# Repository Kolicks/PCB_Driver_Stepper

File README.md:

# 🌀 PCB_Driver_Stepper
**General Stepper Motor Driver Board**

## 🎬 Demo Video
[▶️ Watch Demo](Test_media/NEMA_Stepper.mp4)

<p align="center">
  <video src="https://github.com/user-attachments/assets/646c0d09-2157-4537-b24f-0206d356a9b6" width="600" controls></video>
  <br>
  <em>Demo NEMA Stepper</em>
</p>

---

## 📘 Overview
**PCB_Driver_Stepper** is a general-purpose stepper motor driver board designed in **KiCad 9**.  
This project was created to explore stepper motor control concepts, test design ideas from friends, and gain real experience with PCB design and STM32 microcontroller integration.  
It also represents my first complete project combining **hardware and STM32 firmware** using **STM32CubeIDE**.

<p align="center">
  
  <br>
  <em>3D render of the finished PCB_Driver_Stepper board</em>
</p>

---

## ⚙️ General Information
- First real **KiCad 9** project.
- Implemented to test and validate several design ideas.
- Tested multiple implementations, including **ULN2002** and different **power dissipation** techniques.
- Designed with **4 layers**, though a **2-layer** version could be achieved.
- Typical **FR4 PCB**, **1.6 mm thickness**, standard prepreg stackup.
- Serves as my first practical integration within **STM32CubeIDE**, using **STM32F030K6T6** as the MCU.

<p align="center">
  
  <br>
  <em>Schematic, Block diagram (KiCad 9)</em>
</p>

---

## 🔧 Characteristics
- **Fully functional**, fabricated and tested successfully.
- Tested with **STEPPERONLINE NEMA 17** (2A, 59 N·cm) — achieves over **300 RPM** without load.
- Capable of controlling **two stepper motors** simultaneously.
- Supports up to **2 A per motor**, limited by drivers and onboard potentiometers.
- **Operating voltage:** 12 VDC to 24 VDC (ideal at 24 V).
- Requires **external cooling** (top and bottom) for continuous operation (Alimunium or Copper Radiators used in real test).
- Integrated with **ULN2002A** as input mode (tested and working).
- Uses **pin connectors under driver GND pads** to allow hand-soldering.
- Optional **Schottky diodes** for additional protection and power isolation.

<p align="center">
  
  <br>
  <em>PCB layout design</em>
</p>

---

---

## 🔧 Panelization
- **Fully functional**, designed for **JLCPCB** fabrication process.  
- Created as an **exercise in PCB manufacturing and panelization design**.  
- Explored **V-cut (scoring) limitations**, fabrication tolerances, and how they affect mechanical integrity and assembly.  
- Observed potential **issues with scoring alignment and stress concentration** across panelized edges.  
- **Not required for this project**, as the board’s size and simplicity make panelization **unnecessary and potentially inefficient** for performance or cost.  

<p align="center">
  
  <br>
  <em>Panel layout design</em>
</p>

---

## ⚠️ Known Issues / Notes
- Thermal pads on the **Rsense GND pads** restrict efficient heat dissipation.
- Ideally should maintain a **4-layer design** to ensure proper driver thermal management (as recommended in datasheets).
- Too many bypass Capacitors on the MCU.
- **No status LEDs** (e.g., Power or Fault indicators) currently included — consider adding in future revisions.

---

## 🧩 Files and Structure

<p align="center">
  
</p>

PCB_Driver_Stepper/

├── schematic/ # KiCad schematic files

├── pcb_layout/ # KiCad PCB layout files

├── gerbers/ # Gerber fabrication files

├── images/ # Rendered visuals (3D, SCH, PCB)

├── LICENSE # Hardware license (CERN-OHL-P v2.0)

└── README.md # Project documentation

---

## 📜 License
This hardware design is released under the **CERN Open Hardware License v2 – Permissive (CERN-OHL-P-2.0)**.  
You are free to use, modify, and distribute this design, provided that:
- The license is included with redistributions.
- Proper credit is given to the original author.

More info: https://cern-ohl.web.cern.ch/

---

## 👤 Author
**Project:** PCB_Driver_Stepper  
**Author:** Kolicks  
**Toolchain:** KiCad 9  
**Version:** 9.0  

---

## 🧱 Future Improvements

- **Thermal Design Enhancements:**  
  - Improve **thermal via networks** around driver ICs.  (Done in Panelization)
  - Add **dedicated copper areas** and optional heatsink support for improved temperature control.  (Done in Panelization)

- **User Feedback & Indicators:**  
  - Integrate **status LEDs** for power, enable, and fault signals.  
  - Add a **motor activity indicator** (blinking per step pulse).  

- **Electrical Optimization:**   
  - Consider **thicker copper (2 oz)** for better power handling.  
  - Optimize **Rsense trace routing** to reduce noise coupling.  (Done in Panelization)

- **Mechanical Improvements:**  
  - Adjust mounting hole positions for compatibility with standard enclosures.  
  - Add **labeling and silkscreen clarity** for easier connection identification.  

---

⭐ *If you find this project useful or educational, please consider starring the repository and sharing feedback!*

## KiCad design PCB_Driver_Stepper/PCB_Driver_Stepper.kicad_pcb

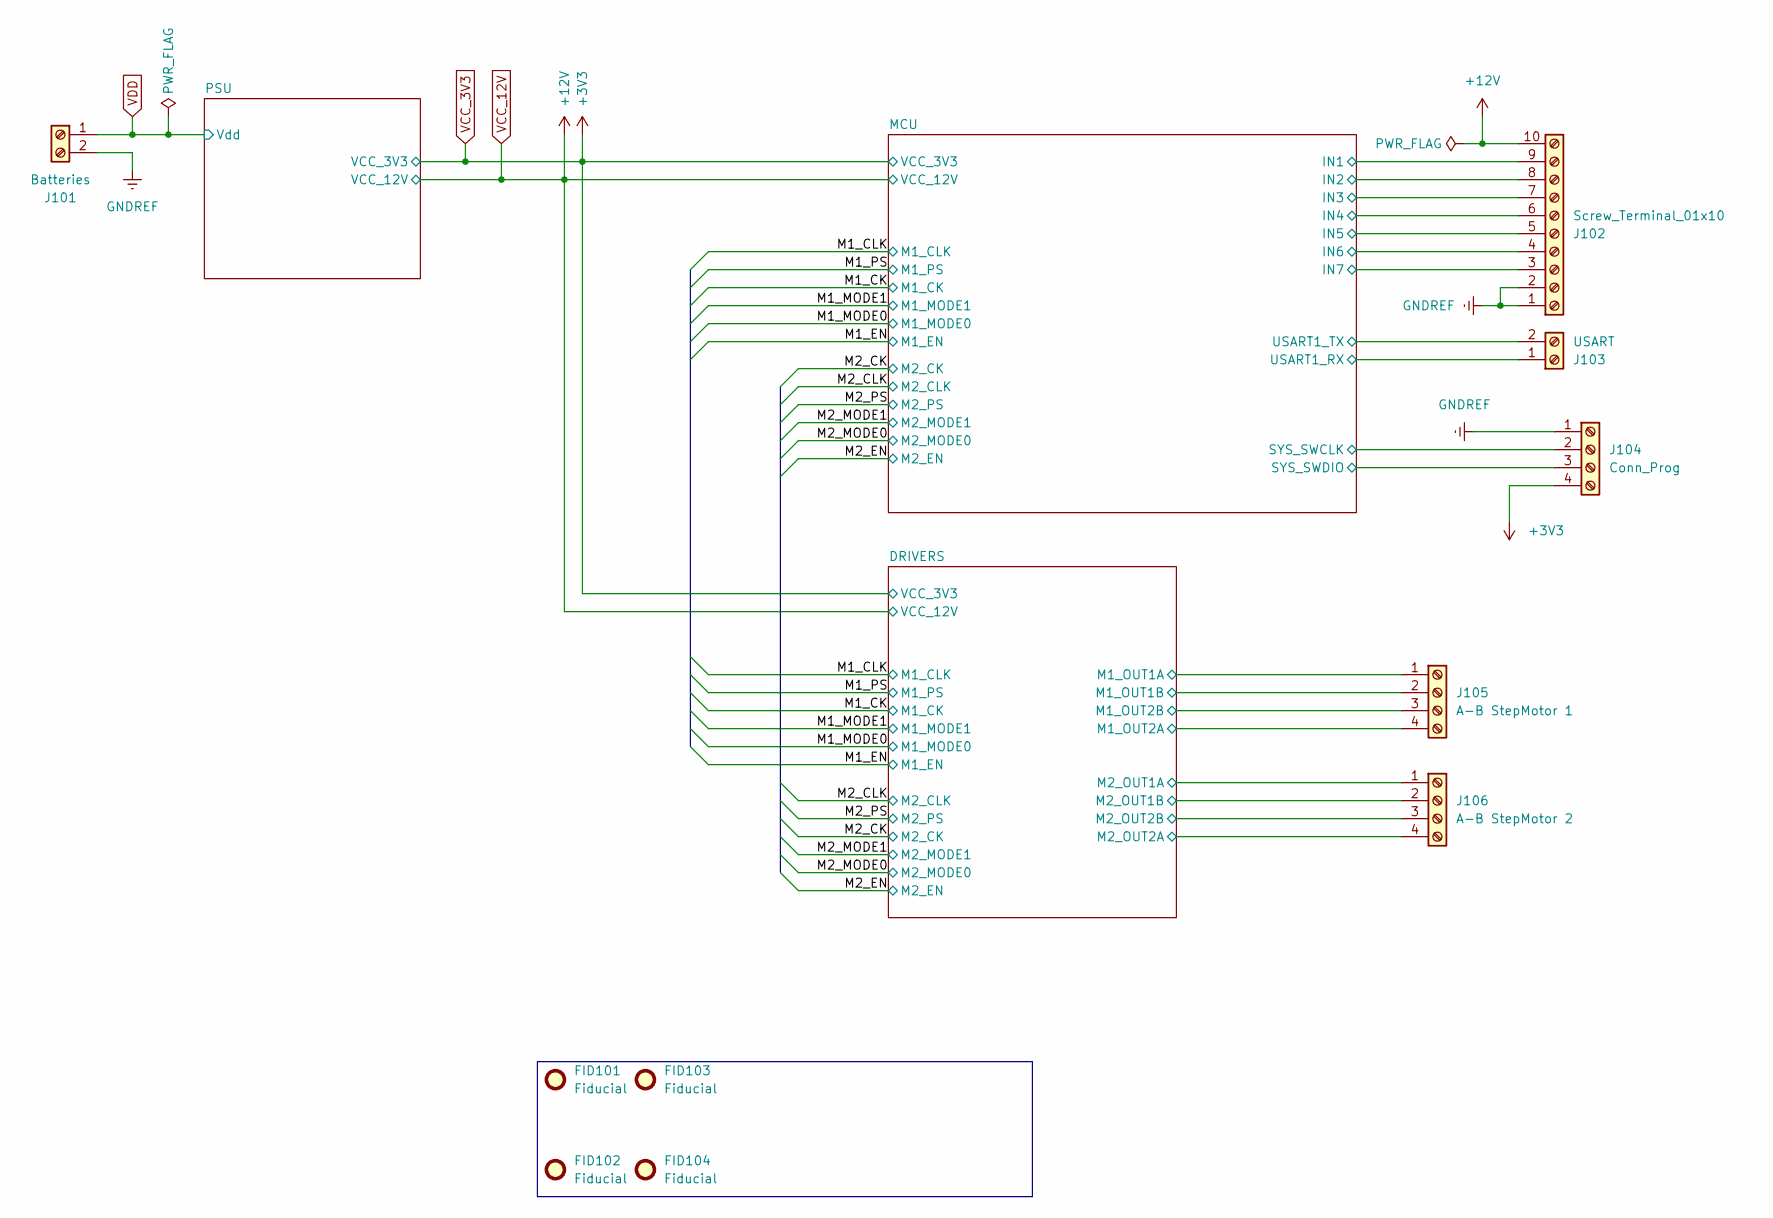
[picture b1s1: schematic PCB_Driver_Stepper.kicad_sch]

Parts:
FID101, FID102, FID103, FID104: Fiducial; Fiducial_1mm_Mask3mm
J101: Batteries; TerminalBlock_TE_282834-2_1x02_P2.54mm_Horizontal
J102: Screw_Terminal_01x10; TerminalBlock_TE_1-282834-0_1x10_P2.54mm_Horizontal
J103: USART; TerminalBlock_TE_282834-2_1x02_P2.54mm_Horizontal
J104: Conn_Prog; TerminalBlock_TE_282834-4_1x04_P2.54mm_Horizontal
J105: A-B StepMotor 1; TerminalBlock_TE_282834-4_1x04_P2.54mm_Horizontal
J106: A-B StepMotor 2; TerminalBlock_TE_282834-4_1x04_P2.54mm_Horizontal

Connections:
/DRIVERS/M1_OUT1A: J105.1; also elsewhere on the board
/DRIVERS/M1_OUT1B: J105.2; also elsewhere on the board
/DRIVERS/M1_OUT2A: J105.4; also elsewhere on the board
/DRIVERS/M1_OUT2B: J105.3; also elsewhere on the board
/DRIVERS/M2_OUT1A: J106.1; also elsewhere on the board
/DRIVERS/M2_OUT1B: J106.2; also elsewhere on the board
/DRIVERS/M2_OUT2A: J106.4; also elsewhere on the board
/DRIVERS/M2_OUT2B: J106.3; also elsewhere on the board
/MCU/IN1: J102.9; also elsewhere on the board
/MCU/IN2: J102.8; also elsewhere on the board
/MCU/IN3: J102.7; also elsewhere on the board
/MCU/IN4: J102.6; also elsewhere on the board
/MCU/IN5: J102.5; also elsewhere on the board
/MCU/IN6: J102.4; also elsewhere on the board
/MCU/IN7: J102.3; also elsewhere on the board
/MCU/SYS_SWCLK: J104.2; also elsewhere on the board
/MCU/SYS_SWDIO: J104.3; also elsewhere on the board
/MCU/USART1_RX: J103.1; also elsewhere on the board
/MCU/USART1_TX: J103.2; also elsewhere on the board
GNDREF: J101.2, J102.1, J102.2, J104.1; also elsewhere on the board
VCC_3V3: J104.4; also elsewhere on the board
VCC_12V: J102.10; also elsewhere on the board
VDD: J101.1; also elsewhere on the board

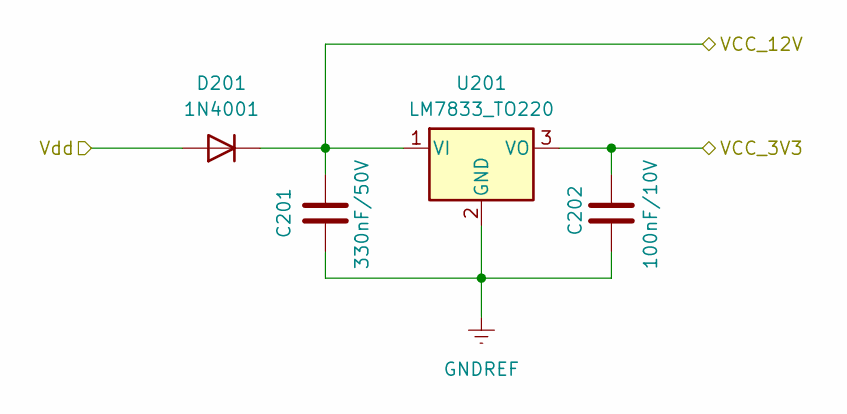
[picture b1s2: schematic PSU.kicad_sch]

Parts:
C201: 330nF/50V; C_0805_2012Metric
C202: 100nF/10V; C_0603_1608Metric
D201: 1N4001; D_SMA
U201: LM7833_TO220; TO-220-3_Vertical

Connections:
GNDREF: C201.2, C202.2, U201.2 (GND); also elsewhere on the board
VCC_3V3: C202.1, U201.3 (VO); also elsewhere on the board
VCC_12V: C201.1, D201.1 (K), U201.1 (VI); also elsewhere on the board
VDD: D201.2 (A); also elsewhere on the board

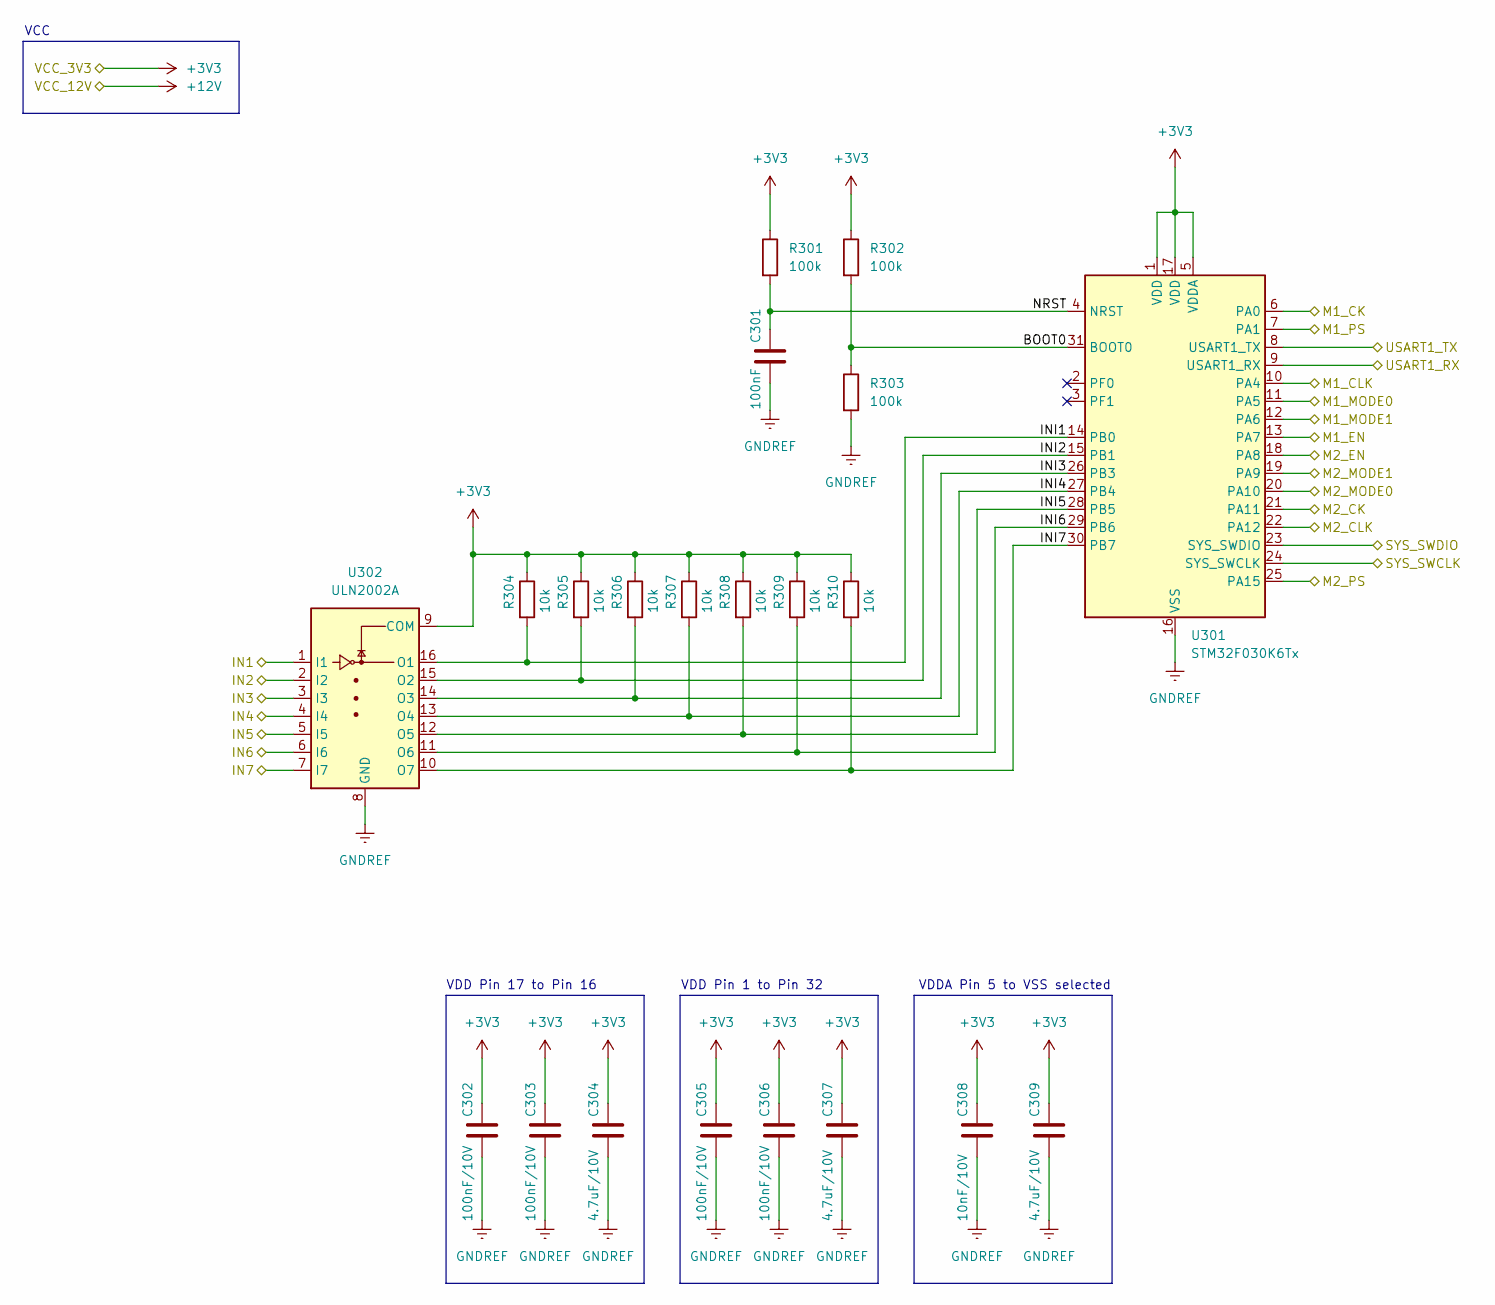
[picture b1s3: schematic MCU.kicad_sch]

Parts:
C301: 100nF; C_0603_1608Metric
C302, C303, C305, C306: 100nF/10V; C_0603_1608Metric
C304, C307, C309: 4.7uF/10V; C_0603_1608Metric
C308: 10nF/10V; C_0603_1608Metric
R301, R302, R303: 100k; R_0603_1608Metric
R304, R305, R306, R307, R308, R309, R310: 10k; R_0603_1608Metric
U301: STM32F030K6Tx; LQFP-32_7x7mm_P0.8mm
U302: ULN2002A; DIP-16_W7.62mm

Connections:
/M1_CK: U301.6 (PA0); also elsewhere on the board
/M1_CLK: U301.10 (PA4); also elsewhere on the board
/M1_EN: U301.13 (PA7); also elsewhere on the board
/M1_MODE0: U301.11 (PA5); also elsewhere on the board
/M1_MODE1: U301.12 (PA6); also elsewhere on the board
/M1_PS: U301.7 (PA1); also elsewhere on the board
/M2_CK: U301.21 (PA11); also elsewhere on the board
/M2_CLK: U301.22 (PA12); also elsewhere on the board
/M2_EN: U301.18 (PA8); also elsewhere on the board
/M2_MODE0: U301.20 (PA10); also elsewhere on the board
/M2_MODE1: U301.19 (PA9); also elsewhere on the board
/M2_PS: U301.25 (PA15); also elsewhere on the board
/MCU/BOOT0: R302.2, R303.1, U301.31 (BOOT0)
/MCU/IN1: U302.1 (I1); also elsewhere on the board
/MCU/IN2: U302.2 (I2); also elsewhere on the board
/MCU/IN3: U302.3 (I3); also elsewhere on the board
/MCU/IN4: U302.4 (I4); also elsewhere on the board
/MCU/IN5: U302.5 (I5); also elsewhere on the board
/MCU/IN6: U302.6 (I6); also elsewhere on the board
/MCU/IN7: U302.7 (I7); also elsewhere on the board
/MCU/INI1: R304.2, U301.14 (PB0), U302.16 (O1)
/MCU/INI2: R305.2, U301.15 (PB1), U302.15 (O2)
/MCU/INI3: R306.2, U301.26 (PB3), U302.14 (O3)
/MCU/INI4: R307.2, U301.27 (PB4), U302.13 (O4)
/MCU/INI5: R308.2, U301.28 (PB5), U302.12 (O5)
/MCU/INI6: R309.2, U301.29 (PB6), U302.11 (O6)
/MCU/INI7: R310.2, U301.30 (PB7), U302.10 (O7)
/MCU/NRST: C301.1, R301.2, U301.4 (NRST)
/MCU/SYS_SWCLK: U301.24 (SYS_SWCLK); also elsewhere on the board
/MCU/SYS_SWDIO: U301.23 (SYS_SWDIO); also elsewhere on the board
/MCU/USART1_RX: U301.9 (USART1_RX); also elsewhere on the board
/MCU/USART1_TX: U301.8 (USART1_TX); also elsewhere on the board
GNDREF: C301.2, C302.2, C303.2, C304.2, C305.2, C306.2, C307.2, C308.2, C309.2, R303.2, U301.16 (VSS), U301.32 (VSS), U302.8 (GND); also elsewhere on the board
VCC_3V3: C302.1, C303.1, C304.1, C305.1, C306.1, C307.1, C308.1, C309.1, R301.1, R302.1, R304.1, R305.1, R306.1, R307.1, R308.1, R309.1, R310.1, U301.1 (VDD), U301.5 (VDDA), U301.17 (VDD), U302.9 (COM); also elsewhere on the board

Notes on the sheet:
VDDA Pin 5 to VSS selected
VDD Pin 1 to Pin 32
VDD Pin 17 to Pin 16
VCC

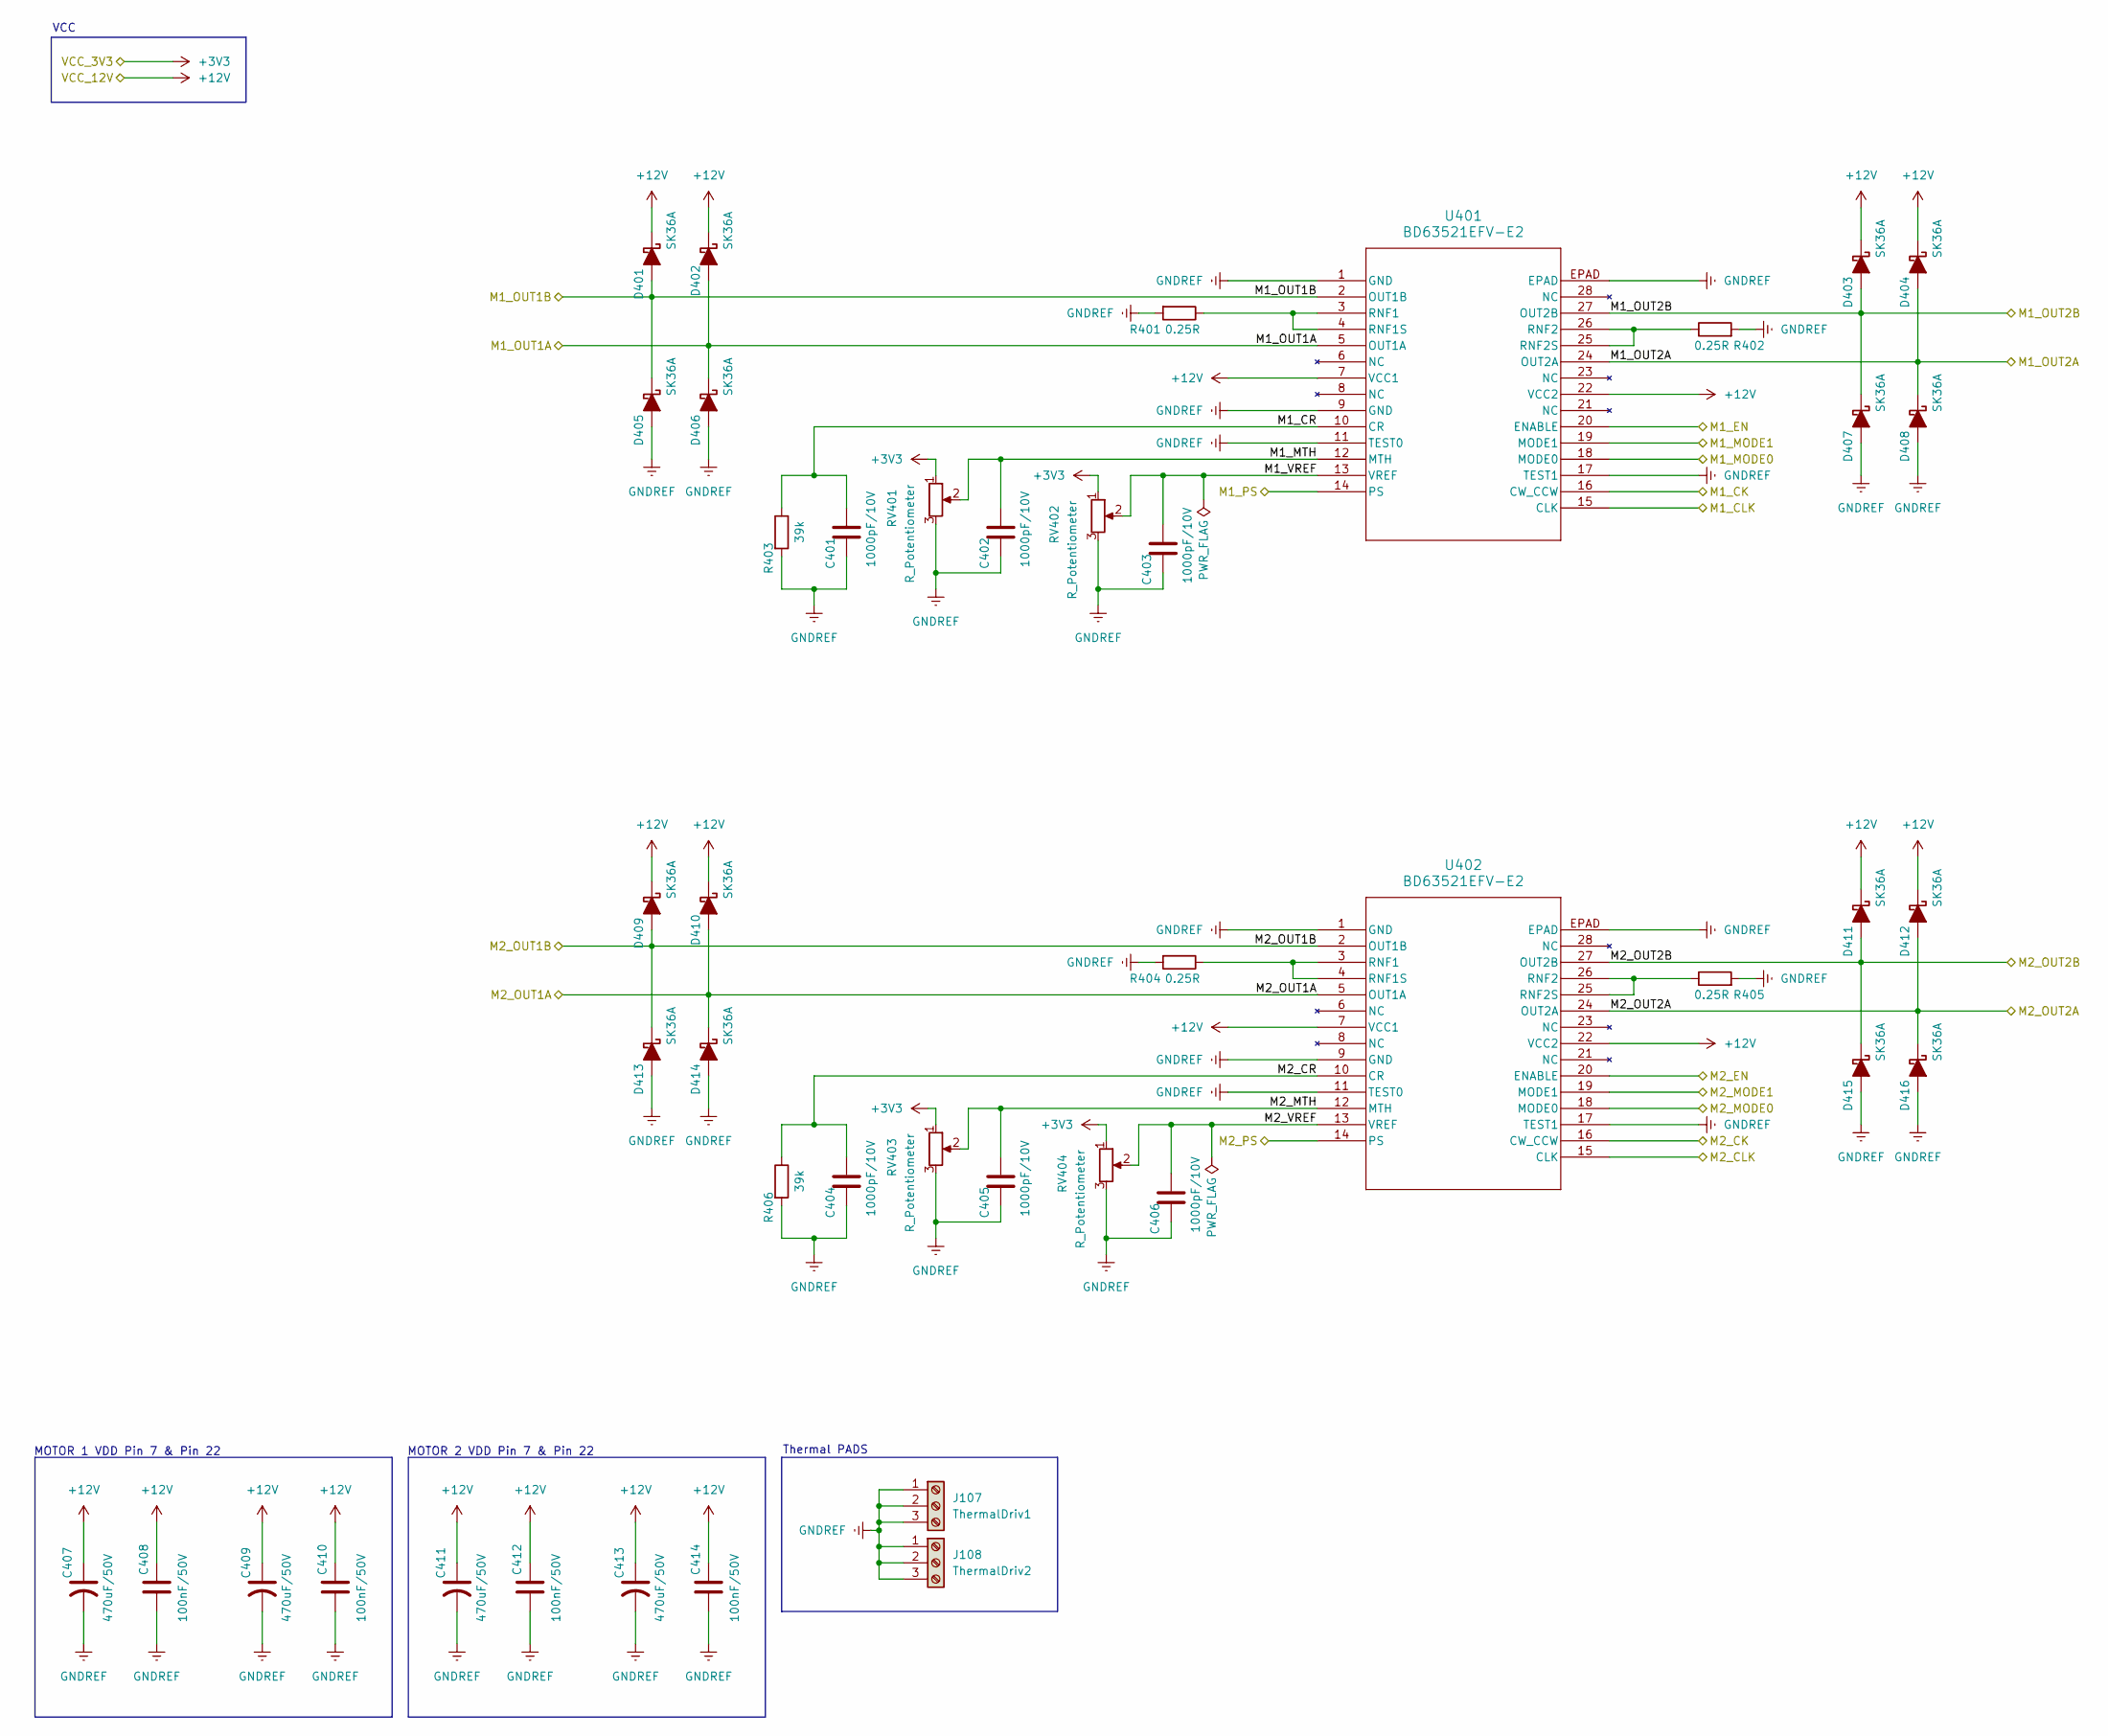
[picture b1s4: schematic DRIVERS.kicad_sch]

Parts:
C401, C402, C403, C404, C405, C406: 1000pF/10V; C_0603_1608Metric
C407, C409, C411, C413: 470uF/50V; C_Elec_10x10.2; Voltage 50V
C408, C410, C412, C414: 100nF/50V; C_0603_1608Metric; Voltage 50V
D401, D402, D403, D404, D405, D406, D407, D408, D409, D410, D411, D412, D413, D414, D415, D416: SK36A; D_SMA
J107: ThermalDriv1; PinHeader_1x03_P1.27mm_Vertical
J108: ThermalDriv2; PinHeader_1x03_P1.27mm_Vertical
R401, R402, R404, R405: 0.25R; R_2512_6332Metric
R403, R406: 39k; R_0603_1608Metric
RV401, RV402, RV403, RV404: R_Potentiometer; Potentiometer_Bourns_TC33X_Vertical
U401, U402: BD63521EFV-E2; HTSSOP-B28_ROM

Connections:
/DRIVERS/M1_CR: C401.1, R403.1, U401.10 (CR)
/DRIVERS/M1_MTH: C402.1, RV401.2, U401.12 (MTH)
/DRIVERS/M1_OUT1A: D402.2 (A), D406.1 (K), U401.5 (OUT1A); also elsewhere on the board
/DRIVERS/M1_OUT1B: D401.2 (A), D405.1 (K), U401.2 (OUT1B); also elsewhere on the board
/DRIVERS/M1_OUT2A: D404.2 (A), D408.1 (K), U401.24 (OUT2A); also elsewhere on the board
/DRIVERS/M1_OUT2B: D403.2 (A), D407.1 (K), U401.27 (OUT2B); also elsewhere on the board
/DRIVERS/M1_VREF: C403.1, RV402.2, U401.13 (VREF)
/DRIVERS/M2_CR: C404.1, R406.1, U402.10 (CR)
/DRIVERS/M2_MTH: C405.1, RV403.2, U402.12 (MTH)
/DRIVERS/M2_OUT1A: D410.2 (A), D414.1 (K), U402.5 (OUT1A); also elsewhere on the board
/DRIVERS/M2_OUT1B: D409.2 (A), D413.1 (K), U402.2 (OUT1B); also elsewhere on the board
/DRIVERS/M2_OUT2A: D412.2 (A), D416.1 (K), U402.24 (OUT2A); also elsewhere on the board
/DRIVERS/M2_OUT2B: D411.2 (A), D415.1 (K), U402.27 (OUT2B); also elsewhere on the board
/DRIVERS/M2_VREF: C406.1, RV404.2, U402.13 (VREF)
/M1_CK: U401.16 (CW_CCW); also elsewhere on the board
/M1_CLK: U401.15 (CLK); also elsewhere on the board
/M1_EN: U401.20 (ENABLE); also elsewhere on the board
/M1_MODE0: U401.18 (MODE0); also elsewhere on the board
/M1_MODE1: U401.19 (MODE1); also elsewhere on the board
/M1_PS: U401.14 (PS); also elsewhere on the board
/M2_CK: U402.16 (CW_CCW); also elsewhere on the board
/M2_CLK: U402.15 (CLK); also elsewhere on the board
/M2_EN: U402.20 (ENABLE); also elsewhere on the board
/M2_MODE0: U402.18 (MODE0); also elsewhere on the board
/M2_MODE1: U402.19 (MODE1); also elsewhere on the board
/M2_PS: U402.14 (PS); also elsewhere on the board
GNDREF: C401.2, C402.2, C403.2, C404.2, C405.2, C406.2, C407.2, C408.2, C409.2, C410.2, C411.2, C412.2, C413.2, C414.2, D405.2 (A), D406.2 (A), D407.2 (A), D408.2 (A), D413.2 (A), D414.2 (A), D415.2 (A), D416.2 (A), J107.1, J107.2, J107.3, J108.1, J108.2, J108.3, R401.2, R402.2, R403.2, R404.2, R405.2, R406.2, RV401.3, RV402.3, RV403.3, RV404.3, U401.1 (GND), U401.9 (GND), U401.11 (TEST0), U401.17 (TEST1), U401.EPAD, U402.1 (GND), U402.9 (GND), U402.11 (TEST0), U402.17 (TEST1), U402.EPAD; also elsewhere on the board
unnamed: R401.1, U401.3 (RNF1), U401.4 (RNF1S)
unnamed: R402.1, U401.25 (RNF2S), U401.26 (RNF2)
unnamed: R404.1, U402.3 (RNF1), U402.4 (RNF1S)
unnamed: R405.1, U402.25 (RNF2S), U402.26 (RNF2)
VCC_3V3: RV401.1, RV402.1, RV403.1, RV404.1; also elsewhere on the board
VCC_12V: C407.1, C408.1, C409.1, C410.1, C411.1, C412.1, C413.1, C414.1, D401.1 (K), D402.1 (K), D403.1 (K), D404.1 (K), D409.1 (K), D410.1 (K), D411.1 (K), D412.1 (K), U401.7 (VCC1), U401.22 (VCC2), U402.7 (VCC1), U402.22 (VCC2); also elsewhere on the board

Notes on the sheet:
MOTOR 2 VDD Pin 7 & Pin 22
VCC
MOTOR 1 VDD Pin 7 & Pin 22
Thermal PADS

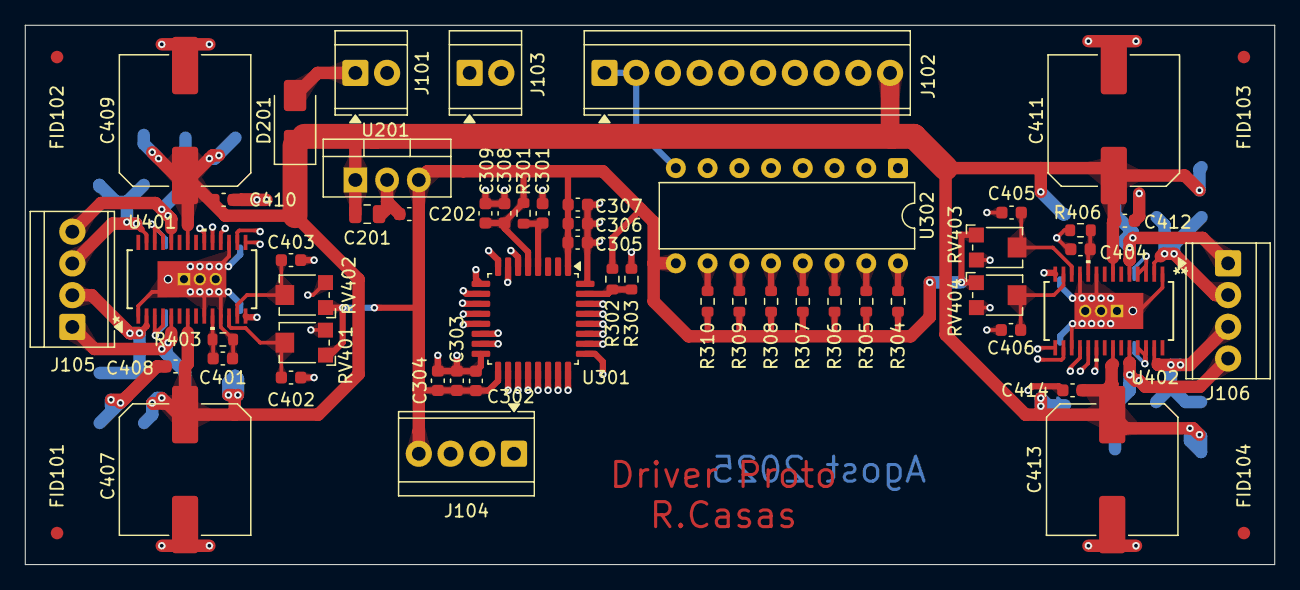
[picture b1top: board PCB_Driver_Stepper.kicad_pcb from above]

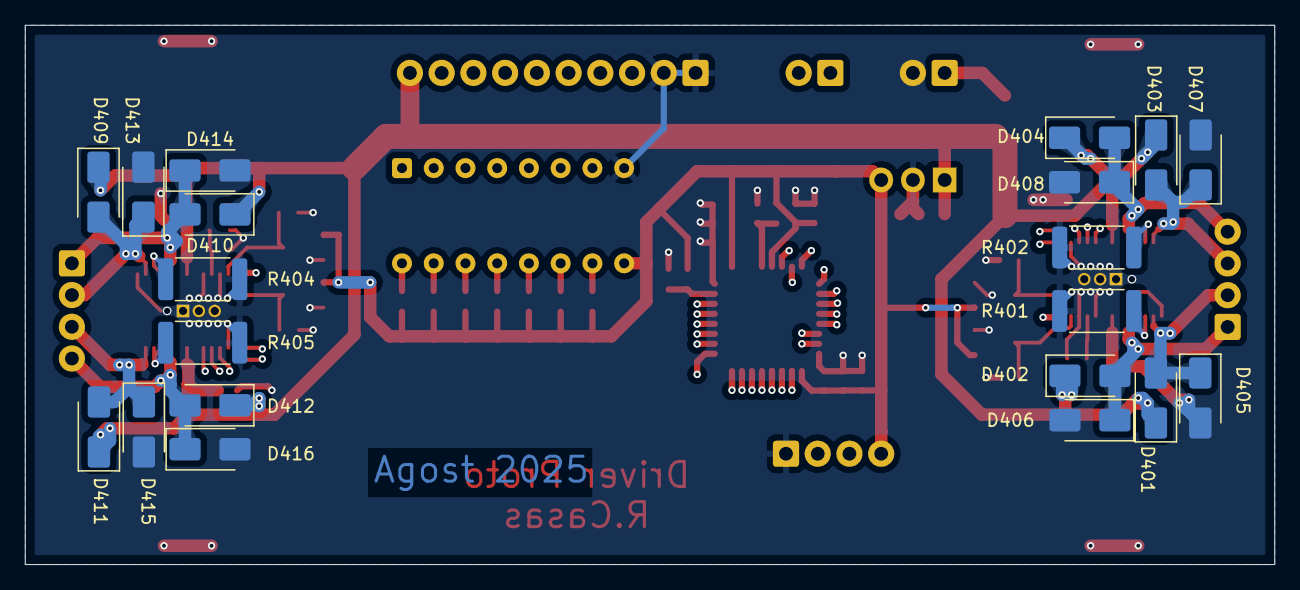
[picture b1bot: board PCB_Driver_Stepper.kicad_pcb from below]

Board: 4 copper layers, 100.0 x 43.2 mm, 79 parts (20 on the bottom side), 54 nets.

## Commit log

2025-10-17 Revise README for PCB_Driver_Stepper project
    Updated README.md to enhance project description and structure.
2025-10-17 All files
2025-10-17 Add demo video section to README
    Added a demo video section with a link to the video.
2025-10-17 Add demo video section to README
2025-11-04 Add files via upload
    Panelization of the project:
    Also som other changes on the PCB:
    - Solid pads for rsense Ground.
    - Added planes of GND on layers 2 & 3 for thermal relief.
